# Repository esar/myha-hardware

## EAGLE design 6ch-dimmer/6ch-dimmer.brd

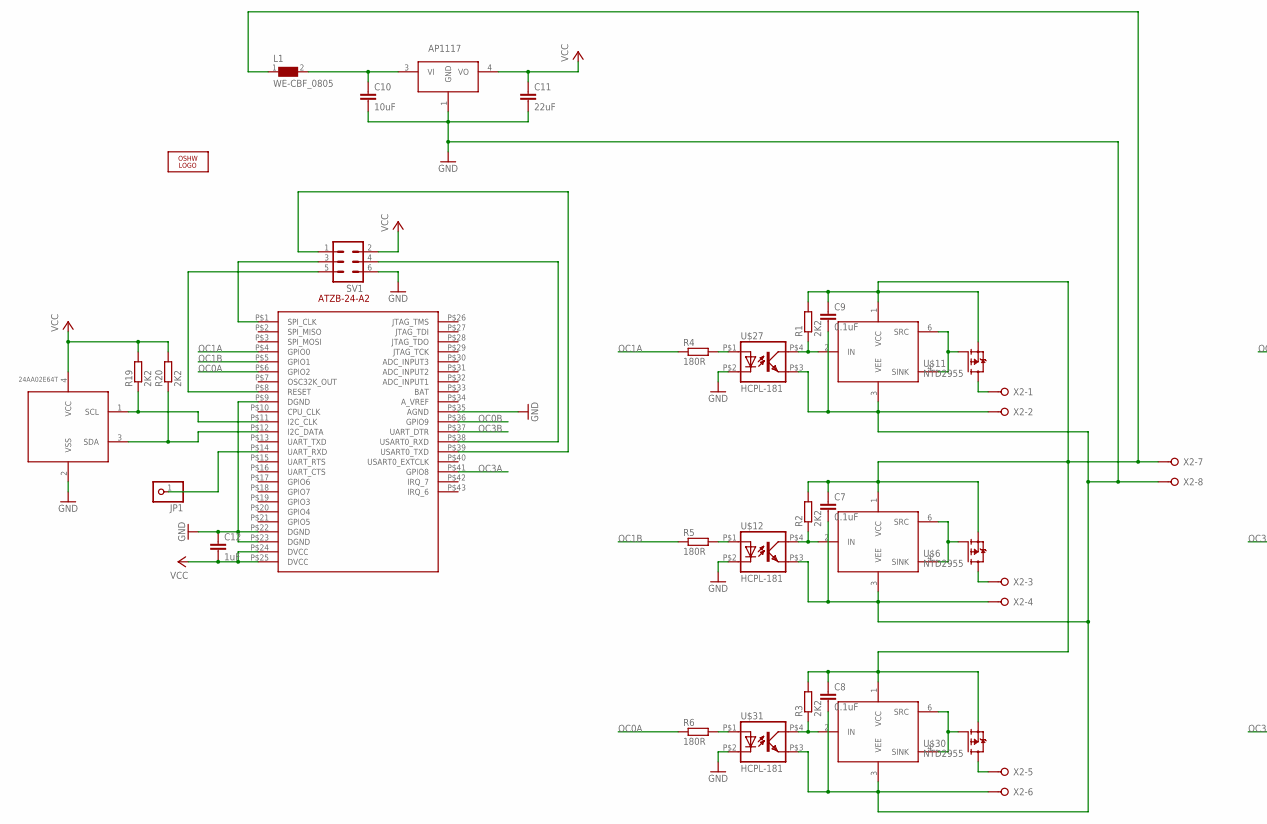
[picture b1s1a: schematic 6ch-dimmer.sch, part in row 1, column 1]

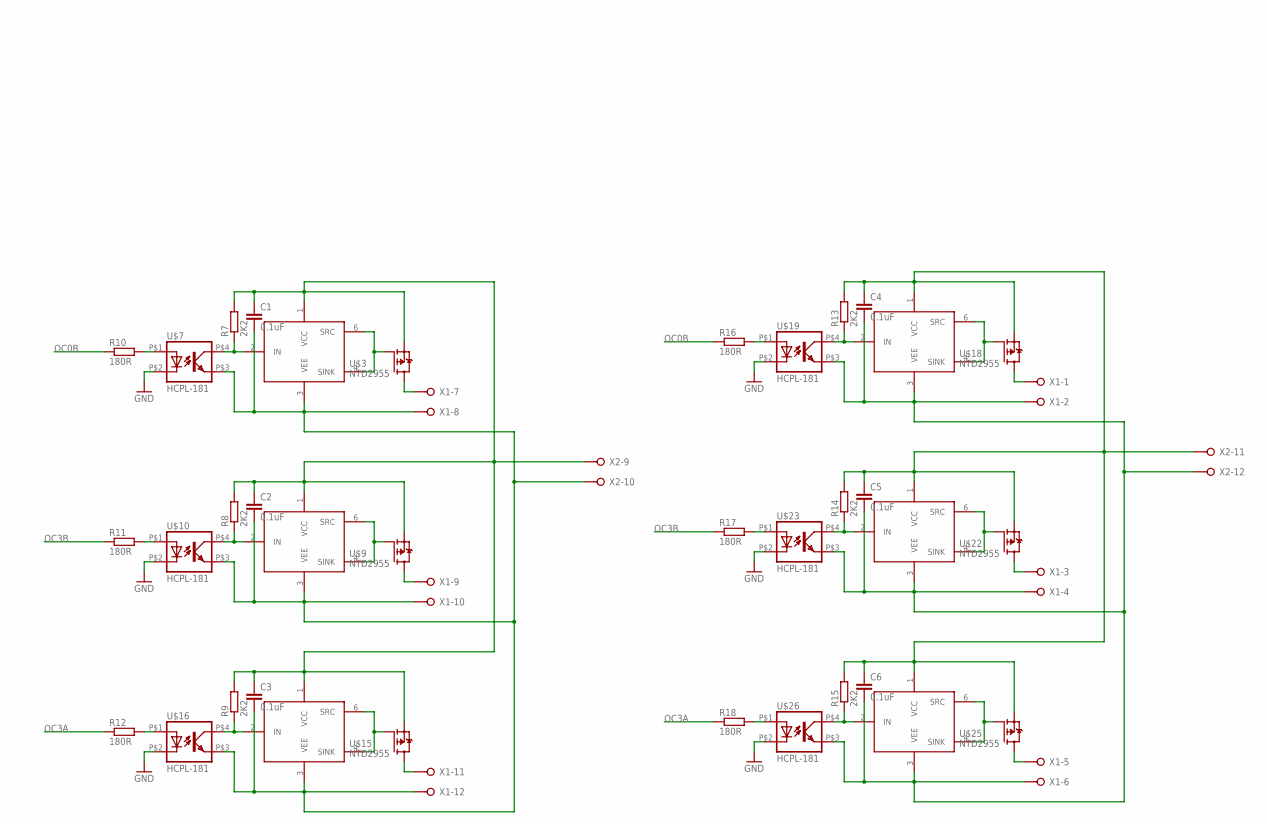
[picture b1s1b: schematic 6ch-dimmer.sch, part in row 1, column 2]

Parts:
C1, C2, C3, C4, C5, C6, C7, C8, C9: 0.1uF; C0603
C10: 10uF; C1210
C11: 22uF; C1210
C12: 1uF; C0603
JP1: PINHD-1X1; 1X01
L1: WE-CBF_0805; 0805
LOGO1: OSHW_LOGO_10MILX0500-NT; OSHW_10X500_NOTEXT
R1, R2, R3, R7, R8, R9, R13, R14, R15, R19, R20: 2K2; R0603
R4, R5, R6, R10, R11, R12, R16, R17, R18: 180R; R0603
SV1: MA03-2
U$1: ATZB-24-A2
U$2, U$4, U$5, U$8, U$13, U$14, U$17, U$21, U$24: ZXGD3005E6; SOT23-6
U$3, U$6, U$9, U$11, U$15, U$18, U$22, U$25, U$30: NTD2955; DPAK
U$7, U$10, U$12, U$16, U$19, U$23, U$26, U$27, U$31: HCPL-181
U$20: 24AA02E64T; SOT23-5L
U$28: AP1117; SOT223
X1, X2: W237-12P

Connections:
GND: C7.2, C8.2, C9.2, C10.2, C11.2, C12.1, SV1.6, U$1.P$9 (DGND), U$1.P$22 (DGND), U$1.P$23 (DGND), U$1.P$35 (AGND), U$4.3 (VEE), U$5.3 (VEE), U$7.P$2 (C), U$10.P$2 (C), U$12.P$2 (C), U$12.P$3 (EMIT), U$13.3 (VEE), U$16.P$2 (C), U$19.P$2 (C), U$20.2 (VSS), U$23.P$2 (C), U$26.P$2 (C), U$27.P$2 (C), U$27.P$3 (EMIT), U$28.1 (GND), U$31.P$2 (C), U$31.P$3 (EMIT), X2.2, X2.4, X2.6, X2.8
unnamed: U$2.4 (SINK), U$2.6 (SRC), U$3.1 (G)
unnamed: R7.1, U$2.2 (IN), U$7.P$4 (COL)
unnamed: U$3.4 (D), X1.7
unnamed: U$4.4 (SINK), U$4.6 (SRC), U$11.1 (G)
unnamed: U$5.4 (SINK), U$5.6 (SRC), U$6.1 (G)
unnamed: R2.1, U$5.2 (IN), U$12.P$4 (COL)
unnamed: U$8.4 (SINK), U$8.6 (SRC), U$9.1 (G)
unnamed: R8.1, U$8.2 (IN), U$10.P$4 (COL)
unnamed: U$9.4 (D), X1.9
unnamed: U$14.4 (SINK), U$14.6 (SRC), U$15.1 (G)
unnamed: R9.1, U$14.2 (IN), U$16.P$4 (COL)
unnamed: C1.1, C2.1, C3.1, R7.2, R8.2, R9.2, U$2.1 (VCC), U$3.3 (S), U$8.1 (VCC), U$9.3 (S), U$14.1 (VCC), U$15.3 (S), X2.9
unnamed: R1.1, U$4.2 (IN), U$27.P$4 (COL)
unnamed: U$11.4 (D), X2.1
unnamed: U$15.4 (D), X1.11
unnamed: R10.2, U$7.P$1 (A)
unnamed: R11.2, U$10.P$1 (A)
unnamed: R12.2, U$16.P$1 (A)
unnamed: JP1.1, U$1.P$14 (UART_RXD)
unnamed: U$6.4 (D), X2.3
unnamed: U$13.4 (SINK), U$13.6 (SRC), U$30.1 (G)
unnamed: R3.1, U$13.2 (IN), U$31.P$4 (COL)
unnamed: C1.2, C2.2, C3.2, U$2.3 (VEE), U$7.P$3 (EMIT), U$8.3 (VEE), U$10.P$3 (EMIT), U$14.3 (VEE), U$16.P$3 (EMIT), X1.8, X1.10, X1.12, X2.10
unnamed: C7.1, C8.1, C9.1, L1.1, R1.2, R2.2, R3.2, U$4.1 (VCC), U$5.1 (VCC), U$6.3 (S), U$11.3 (S), U$13.1 (VCC), U$30.3 (S), X2.7
unnamed: U$17.4 (SINK), U$17.6 (SRC), U$18.1 (G)
unnamed: U$30.4 (D), X2.5
unnamed: R13.1, U$17.2 (IN), U$19.P$4 (COL)
unnamed: U$18.4 (D), X1.1
unnamed: R4.2, U$27.P$1 (A)
unnamed: U$21.4 (SINK), U$21.6 (SRC), U$22.1 (G)
unnamed: R5.2, U$12.P$1 (A)
unnamed: R6.2, U$31.P$1 (A)
unnamed: R14.1, U$21.2 (IN), U$23.P$4 (COL)
unnamed: U$22.4 (D), X1.3
unnamed: U$24.4 (SINK), U$24.6 (SRC), U$25.1 (G)
unnamed: R15.1, U$24.2 (IN), U$26.P$4 (COL)
unnamed: C4.1, C5.1, C6.1, R13.2, R14.2, R15.2, U$17.1 (VCC), U$18.3 (S), U$21.1 (VCC), U$22.3 (S), U$24.1 (VCC), U$25.3 (S), X2.11
unnamed: U$25.4 (D), X1.5
unnamed: R16.2, U$19.P$1 (A)
unnamed: R17.2, U$23.P$1 (A)
unnamed: R18.2, U$26.P$1 (A)
unnamed: C4.2, C5.2, C6.2, U$17.3 (VEE), U$19.P$3 (EMIT), U$21.3 (VEE), U$23.P$3 (EMIT), U$24.3 (VEE), U$26.P$3 (EMIT), X1.2, X1.4, X1.6, X2.12
unnamed: R19.1, U$1.P$11 (I2C_CLK), U$20.1 (SCL)
unnamed: R20.1, U$1.P$12 (I2C_DATA), U$20.3 (SDA)
unnamed: C10.1, L1.2, U$28.3 (VI)
unnamed: SV1.1, U$1.P$39 (USART0_TXD)
unnamed: SV1.4, U$1.P$38 (USART0_RXD)
unnamed: SV1.3, U$1.P$1 (SPI_CLK)
unnamed: SV1.5, U$1.P$8 (RESET)
OC0A: R6.1, U$1.P$6 (GPIO2)
OC0B: R10.1, R16.1, U$1.P$36 (GPIO9)
OC1A: R4.1, U$1.P$4 (GPIO0)
OC1B: R5.1, U$1.P$5 (GPIO1)
OC3A: R12.1, R18.1, U$1.P$41 (GPIO8)
OC3B: R11.1, R17.1, U$1.P$37 (UART_DTR)
VCC: C11.1, C12.2, R19.2, R20.2, SV1.2, U$1.P$24 (DVCC), U$1.P$25 (DVCC), U$20.4 (VCC), U$28.4 (VO)

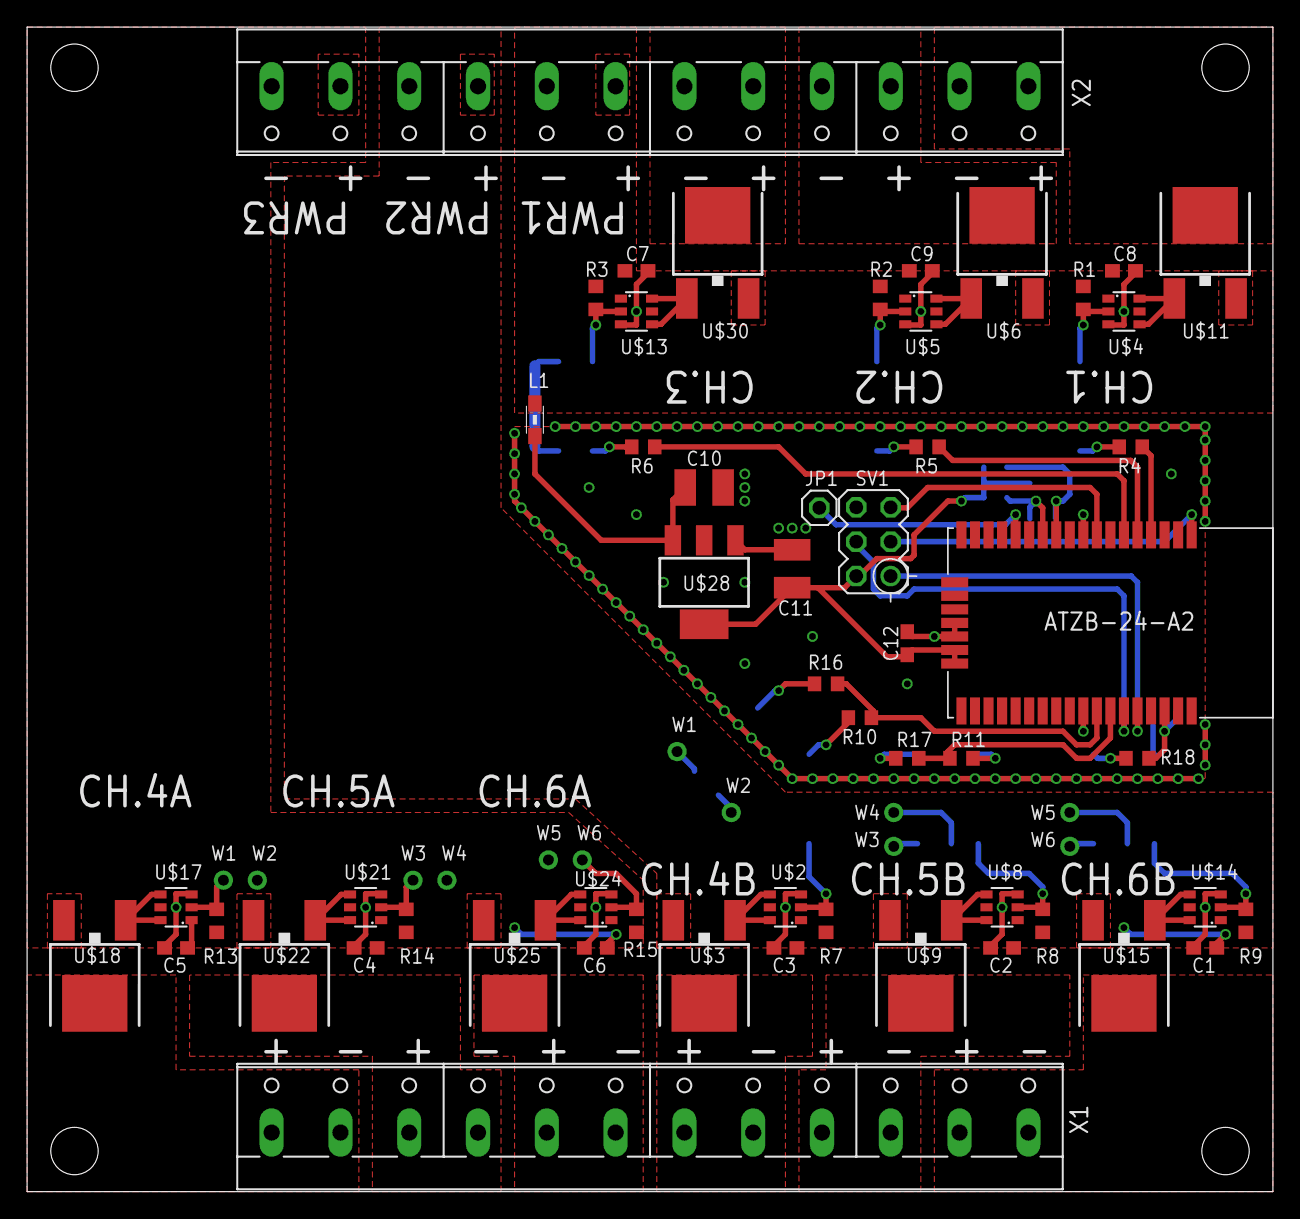
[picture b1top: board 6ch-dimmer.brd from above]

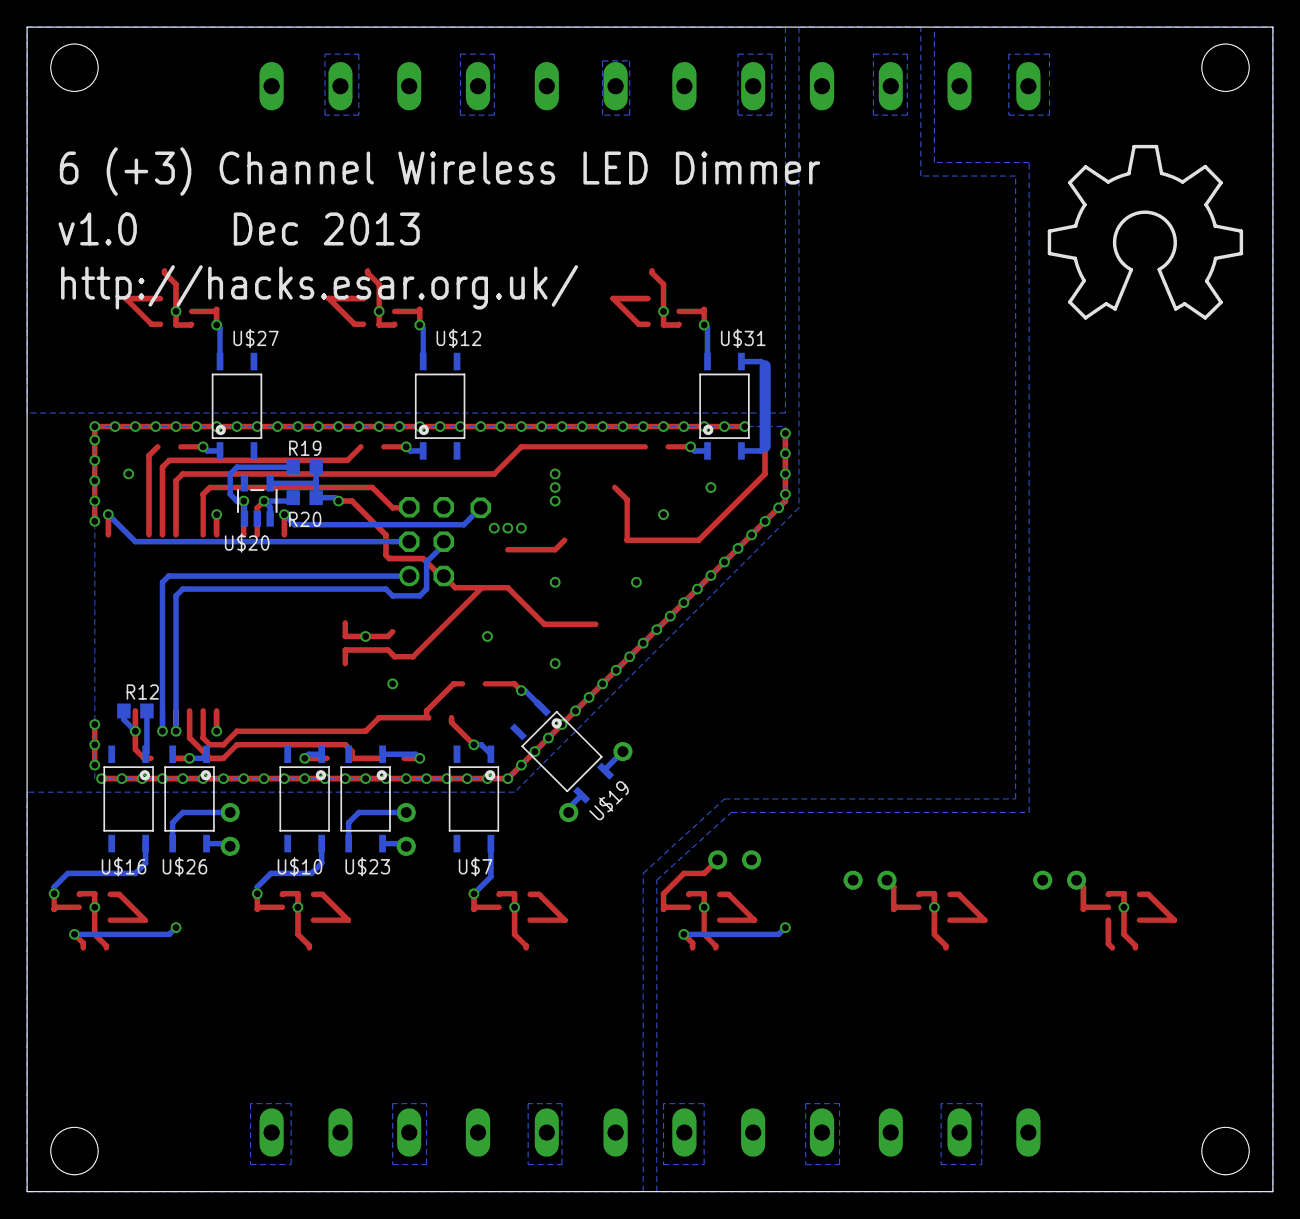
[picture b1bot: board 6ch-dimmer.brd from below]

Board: 2 copper layers, 92.0 x 86.0 mm, 68 parts (14 on the bottom side), 57 nets.

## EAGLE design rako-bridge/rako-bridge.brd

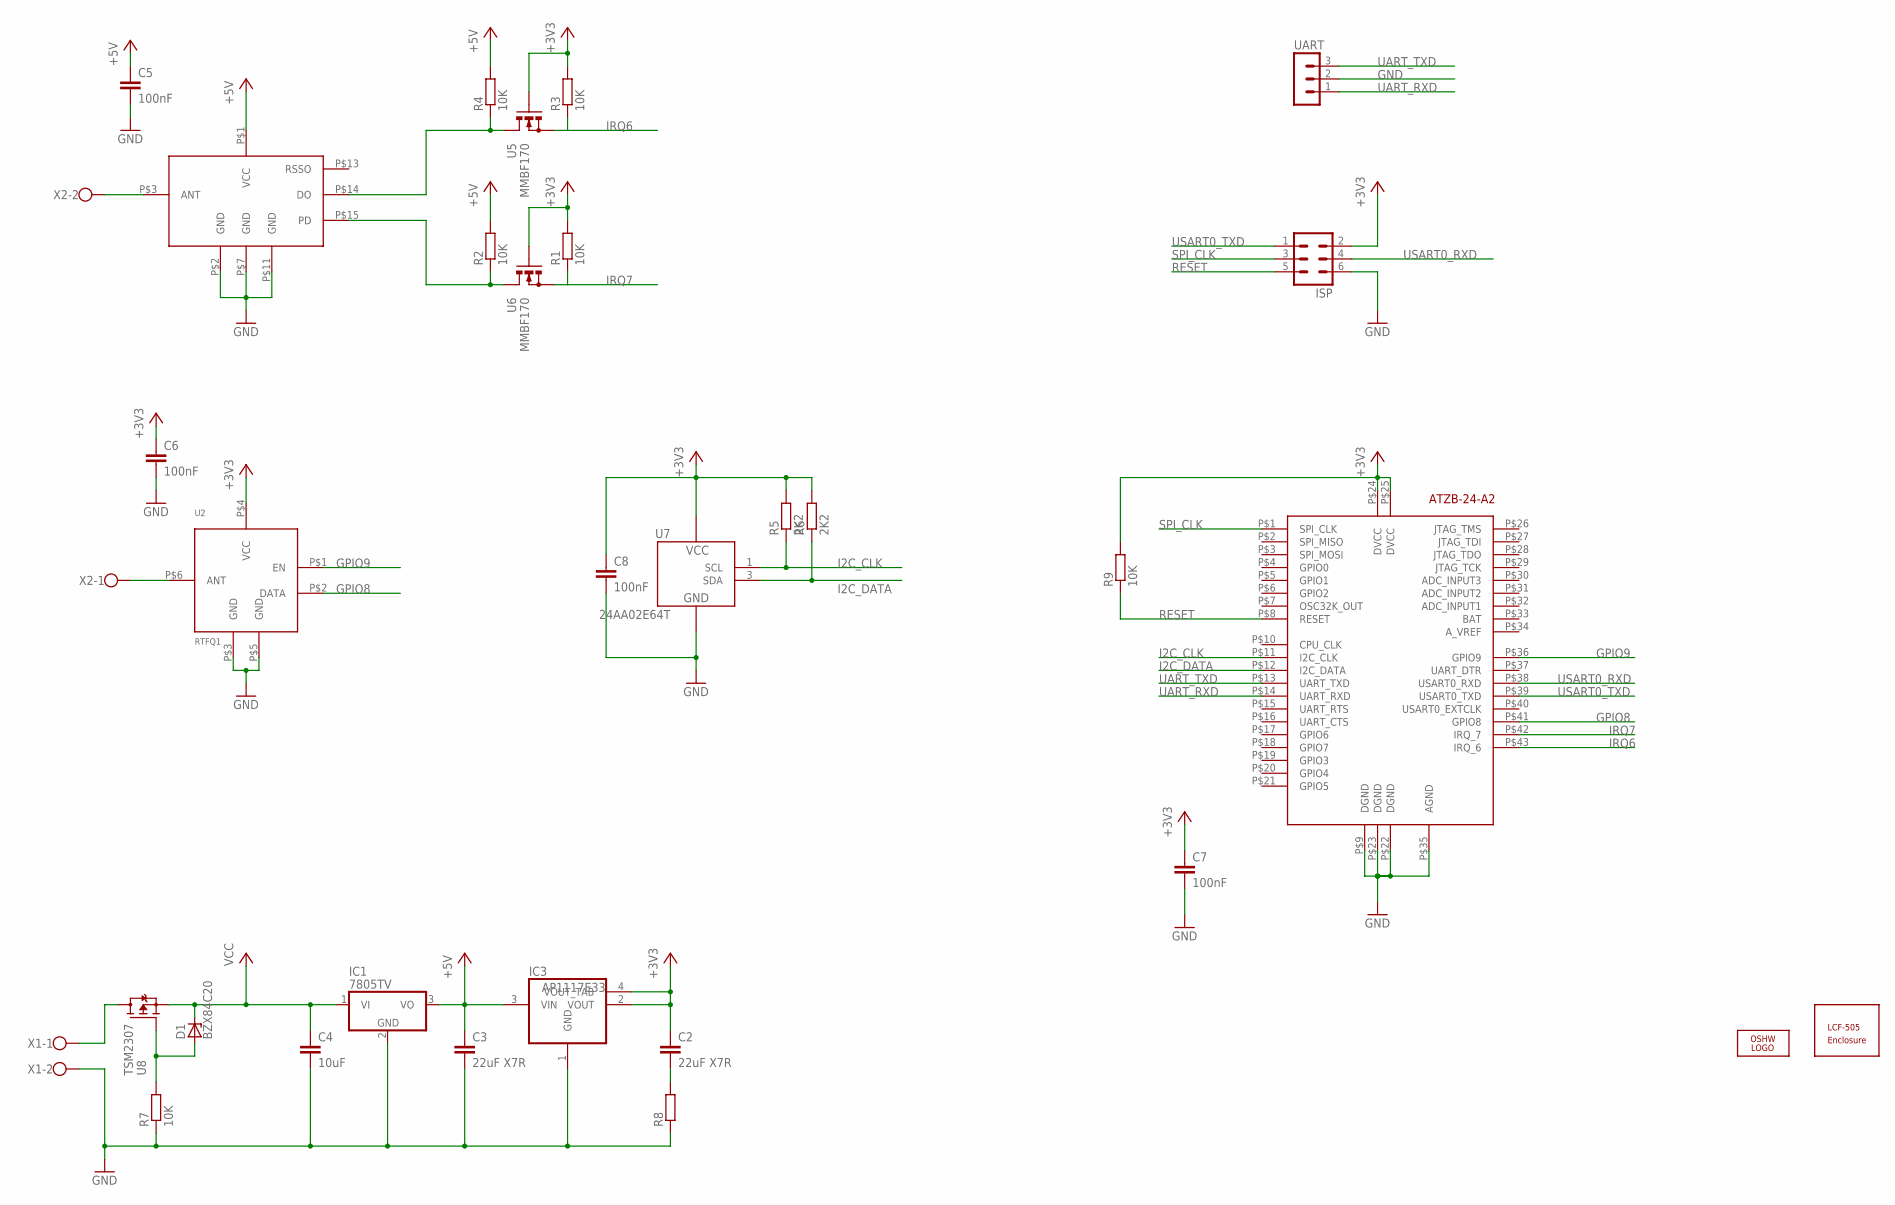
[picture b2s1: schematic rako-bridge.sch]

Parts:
C2, C3: 22uF X7R; C1210
C4: 10uF; C1210
C5, C6, C7, C8: 100nF; C0603
D1: BZX84C20; SOT23
IC1: 7805TV; TO220V
IC3: AP1117E33; SOT223
ISP: MA03-2
LOGO1: OSHW_LOGO_FILLX0200-NT; OSHW_FILLX200_NOTEXT
R1, R2, R3, R4, R7, R9: 10K; R0603
R5, R6: 2K2; R0603
R8: R-EU_R0603; R0603
U2: RTFQ1
U4: RRFQ1
U5, U6: MMBF170; SOT23
U7: 24AA02E64T; SOT23-5L
U8: TSM2307; SOT23
U$1: BOX-LCF-505
U$3: ATZB-24-A2
UART: MA03-1
X1, X2: W237-102

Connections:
+3V3: C2.1, C6.1, C7.1, C8.1, IC3.2 (VOUT), IC3.4 (VOUT_TAB), ISP.2, R1.2, R3.2, R5.2, R6.2, R9.2, U2.P$4 (VCC), U5.1 (G), U6.1 (G), U7.4 (VCC), U$3.P$24 (DVCC), U$3.P$25 (DVCC)
+5V: C3.1, C5.1, IC1.3 (VO), IC3.3 (VIN), R2.2, R4.2, U4.P$1 (VCC)
GND: C3.2, C4.2, C5.2, C6.2, C7.2, C8.2, IC1.2 (GND), IC3.1 (GND), ISP.6, R7.1, R8.1, U2.P$3 (GND), U2.P$5 (GND), U4.P$2 (GND), U4.P$7 (GND), U4.P$11 (GND), U7.2 (VSS), U$3.P$9 (DGND), U$3.P$22 (DGND), U$3.P$23 (DGND), U$3.P$35 (AGND), UART.2, X1.2
GPIO8: U2.P$2 (DATA), U$3.P$41 (GPIO8)
GPIO9: U2.P$1 (EN), U$3.P$36 (GPIO9)
I2C_CLK: R5.1, U7.1 (SCL), U$3.P$11 (I2C_CLK)
I2C_DATA: R6.1, U7.3 (SDA), U$3.P$12 (I2C_DATA)
IRQ6: R3.1, U5.2 (S), U$3.P$43 (IRQ_6)
IRQ7: R1.1, U6.2 (S), U$3.P$42 (IRQ_7)
unnamed: U4.P$3 (ANT), X2.2
unnamed: U2.P$6 (ANT), X2.1
unnamed: D1.1 (A), R7.2, U8.1 (G)
unnamed: U8.3 (D), X1.1
unnamed: R2.1, U4.P$15 (PD), U6.3 (D)
unnamed: R4.1, U4.P$14 (DO), U5.3 (D)
unnamed: C2.2, R8.2
RESET: ISP.5, R9.1, U$3.P$8 (RESET)
SPI_CLK: ISP.3, U$3.P$1 (SPI_CLK)
UART_RXD: U$3.P$14 (UART_RXD), UART.1
UART_TXD: U$3.P$13 (UART_TXD), UART.3
USART0_RXD: ISP.4, U$3.P$38 (USART0_RXD)
USART0_TXD: ISP.1, U$3.P$39 (USART0_TXD)
VCC: C4.1, D1.3 (C), IC1.1 (VI), U8.2 (S)

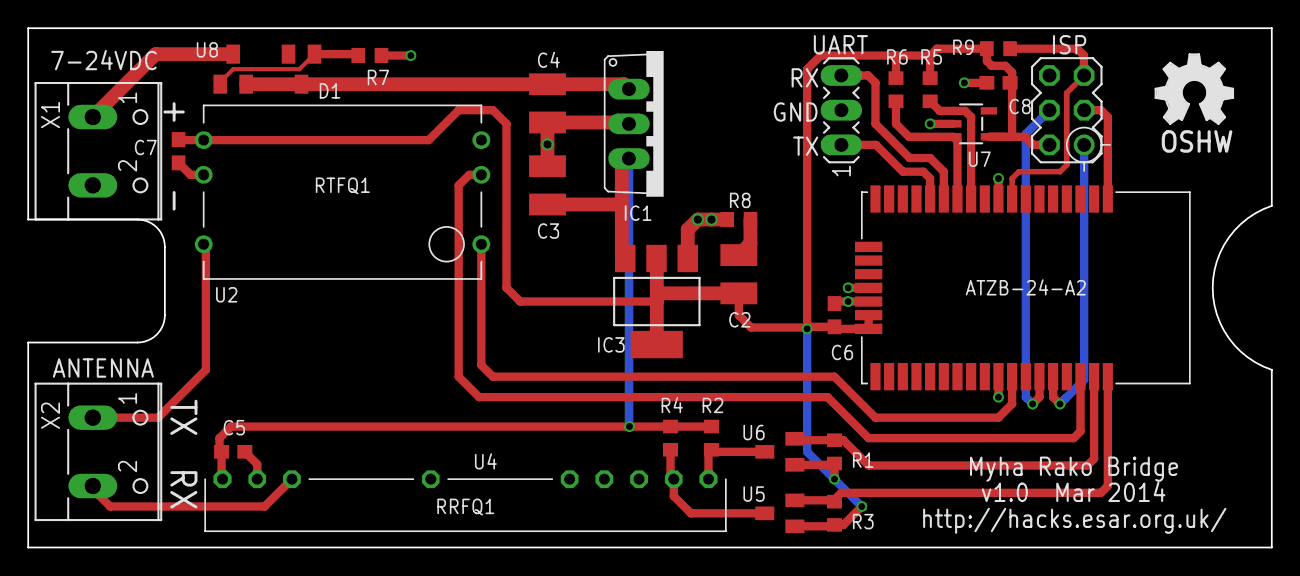
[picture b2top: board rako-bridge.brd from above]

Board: 2 copper layers, 91.0 x 38.0 mm, 32 parts (0 on the bottom side), 23 nets.

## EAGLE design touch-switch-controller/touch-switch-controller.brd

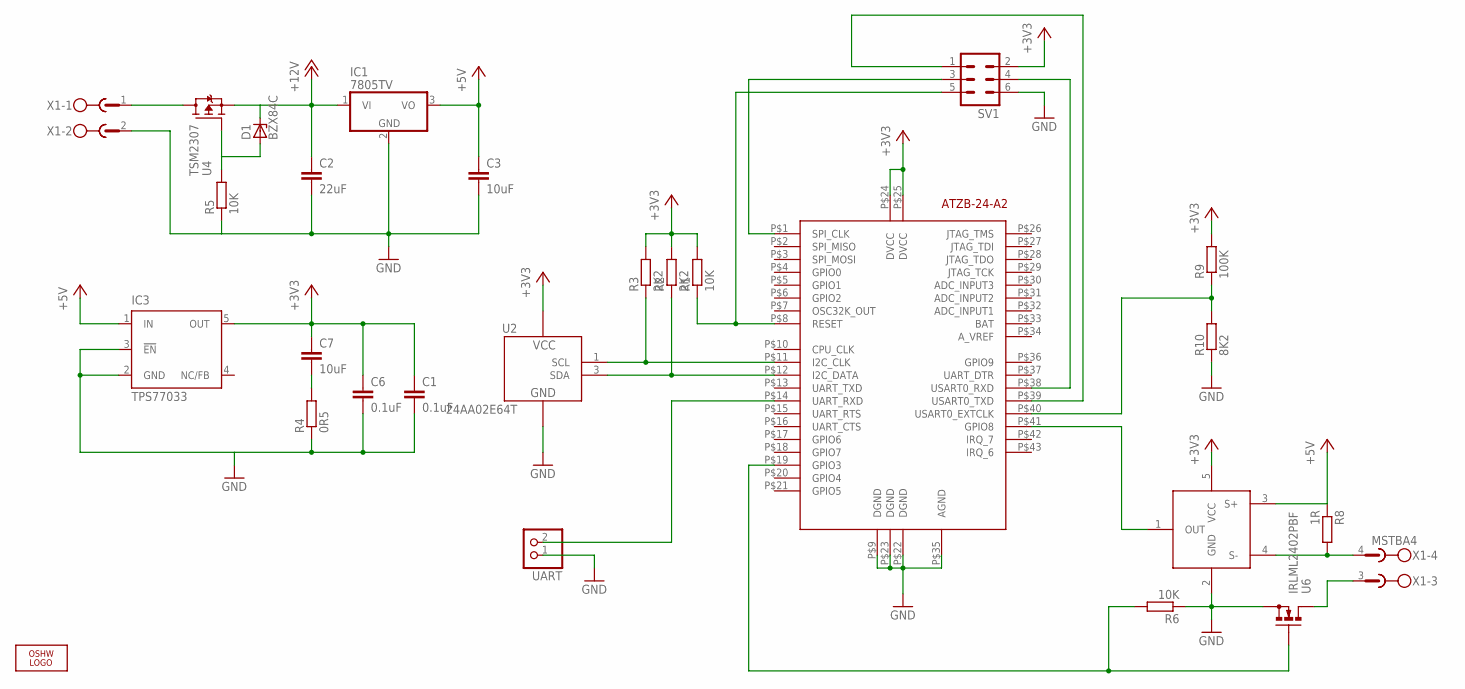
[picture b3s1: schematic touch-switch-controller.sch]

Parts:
C1, C6: 0.1uF; C0603
C2: 22uF; C1210
C3, C7: 10uF; C1210
D1: BZX84C; SOT23
IC1: 7805TV; TO220V
IC3: TPS77033; SOT23-DBV
LOGO1: OSHW_LOGO_FILLX0100-NT; OSHW_FILLX100_NOTEXT
R1, R5, R6: 10K; R0603
R2, R3: 2K2; R0603
R4: 0R5; R0603
R8: 1R; R0603
R9: 100K; R0603
R10: 8K2; R0603
SV1: MA03-2
U1: ZXCT1086; SOT23-5L
U2: 24AA02E64T; SOT23-5L
U4: TSM2307; SOT23
U6: IRLML2402PBF; SOT23
U$3: ATZB-24-A2
UART: PINHD-1X2; 1X02
X1: MSTBA4

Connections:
+3V3: C1.1, C6.1, C7.1, IC3.5 (OUT), R1.2, R2.2, R3.2, R9.2, SV1.2, U1.5 (VCC), U2.4 (VCC), U$3.P$24 (DVCC), U$3.P$25 (DVCC)
+5V: C3.1, IC1.3 (VO), IC3.1 (IN), R8.1, U1.3 (S+)
+12V: C2.1, D1.3 (C), IC1.1 (VI), U4.2 (S)
GND: C1.2, C2.2, C3.2, C6.2, IC1.2 (GND), IC3.2 (GND), IC3.3 (!EN), R4.1, R5.1, R6.1, R10.1, SV1.6, U1.2 (GND), U2.2 (VSS), U6.2 (S), U$3.P$9 (DGND), U$3.P$22 (DGND), U$3.P$23 (DGND), U$3.P$35 (AGND), UART.1, X1.2
unnamed: R9.1, R10.2, U$3.P$40 (USART0_EXTCLK)
unnamed: U1.1 (OUT), U$3.P$41 (GPIO8)
unnamed: R6.2, U6.1 (G), U$3.P$19 (GPIO3)
unnamed: U4.3 (D), X1.1
unnamed: SV1.1, U$3.P$39 (USART0_TXD)
unnamed: SV1.4, U$3.P$38 (USART0_RXD)
unnamed: R3.1, U2.1 (SCL), U$3.P$11 (I2C_CLK)
unnamed: SV1.3, U$3.P$1 (SPI_CLK)
unnamed: R1.1, SV1.5, U$3.P$8 (RESET)
unnamed: R2.1, U2.3 (SDA), U$3.P$12 (I2C_DATA)
unnamed: C7.2, R4.2
unnamed: D1.1 (A), R5.2, U4.1 (G)
unnamed: U$3.P$14 (UART_RXD), UART.2
unnamed: U6.3 (D), X1.3
unnamed: R8.2, U1.4 (S-), X1.4

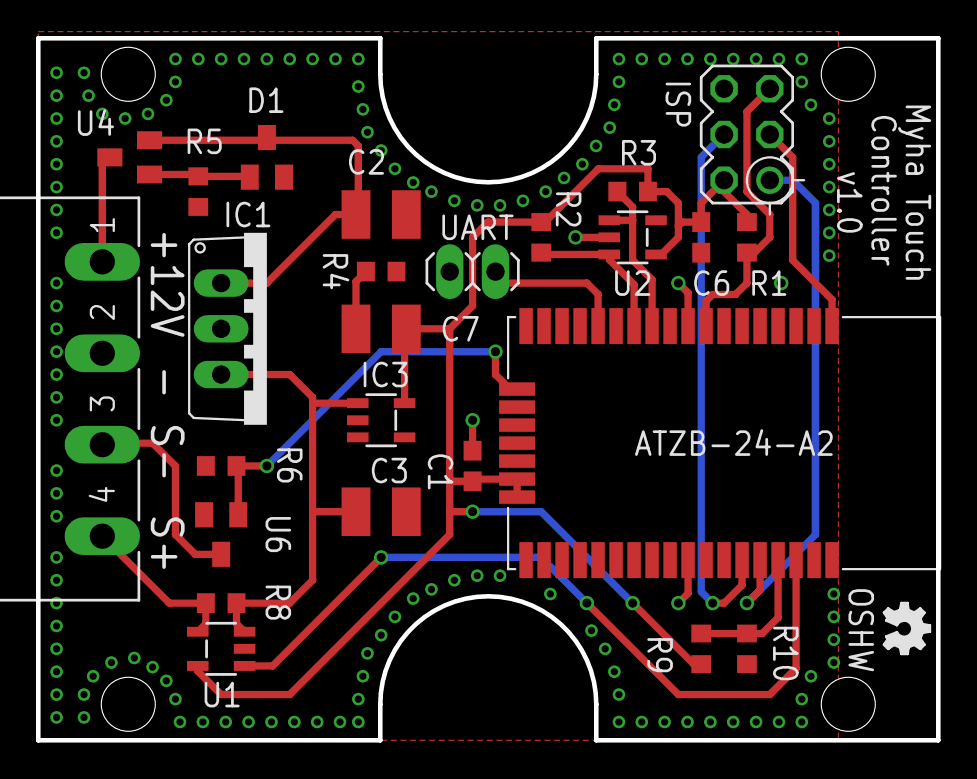
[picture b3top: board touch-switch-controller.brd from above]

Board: 2 copper layers, 50.0 x 39.0 mm, 26 parts (0 on the bottom side), 19 nets.

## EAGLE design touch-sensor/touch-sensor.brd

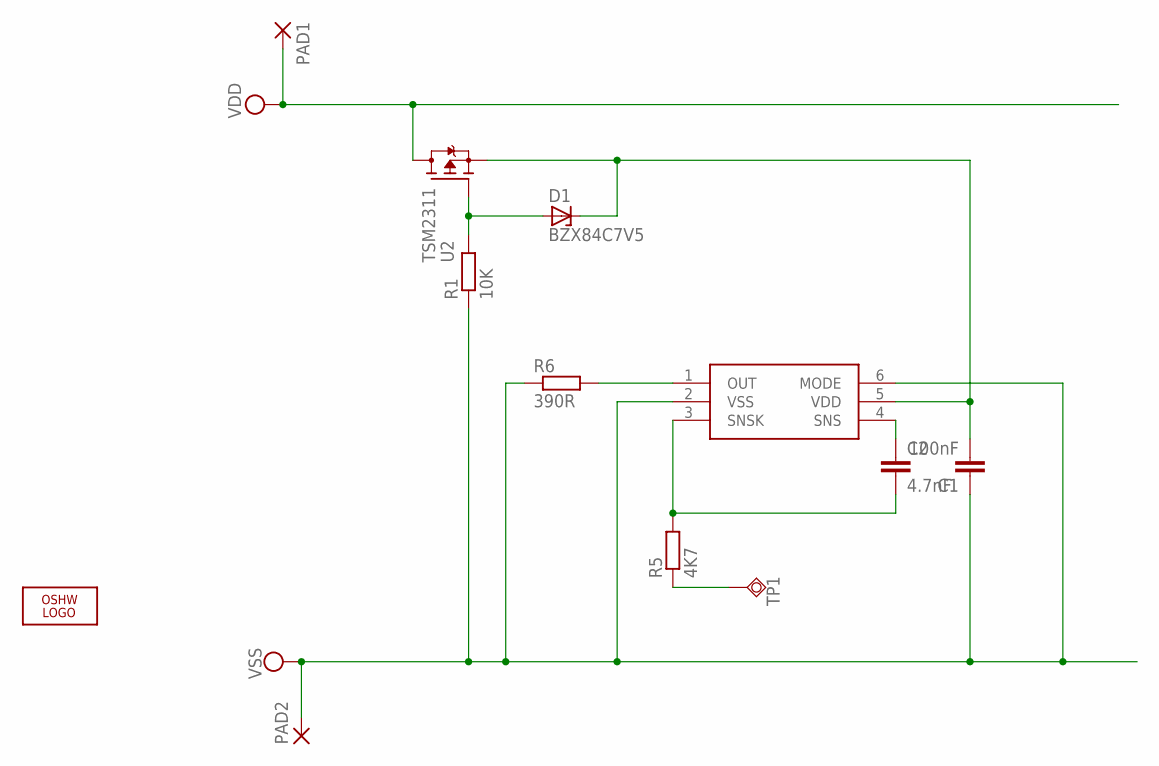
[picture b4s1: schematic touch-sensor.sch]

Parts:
C1: 100nF; C0603
C2: 4.7nF; C0603
D1: BZX84C7V5; SOT23
LOGO1: OSHW_LOGO_10MILX0200-NT; OSHW_10X200_NOTEXT
PAD1, PAD2: 3,81/1,3
R1: 10K; R0603
R5: 4K7; R0603
R6: 390R; R0603
TP1: TPSQTP20SQ; TP20SQ
U1: AT42QT1011; SOT23-6
U2: TSM2311; SOT23

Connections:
unnamed: C1.2, D1.3 (C), U1.5 (VDD), U2.2 (S)
unnamed: D1.1 (A), R1.2, U2.1 (G)
unnamed: C2.1, U1.4 (SNS)
unnamed: C2.2, R5.2, U1.3 (SNSK)
unnamed: R6.2, U1.1 (OUT)
unnamed: R5.1, TP1.TP
VDD: PAD1.1, U2.3 (D)
VSS: C1.1, PAD2.1, R1.1, R6.1, U1.2 (VSS), U1.6 (MODE)

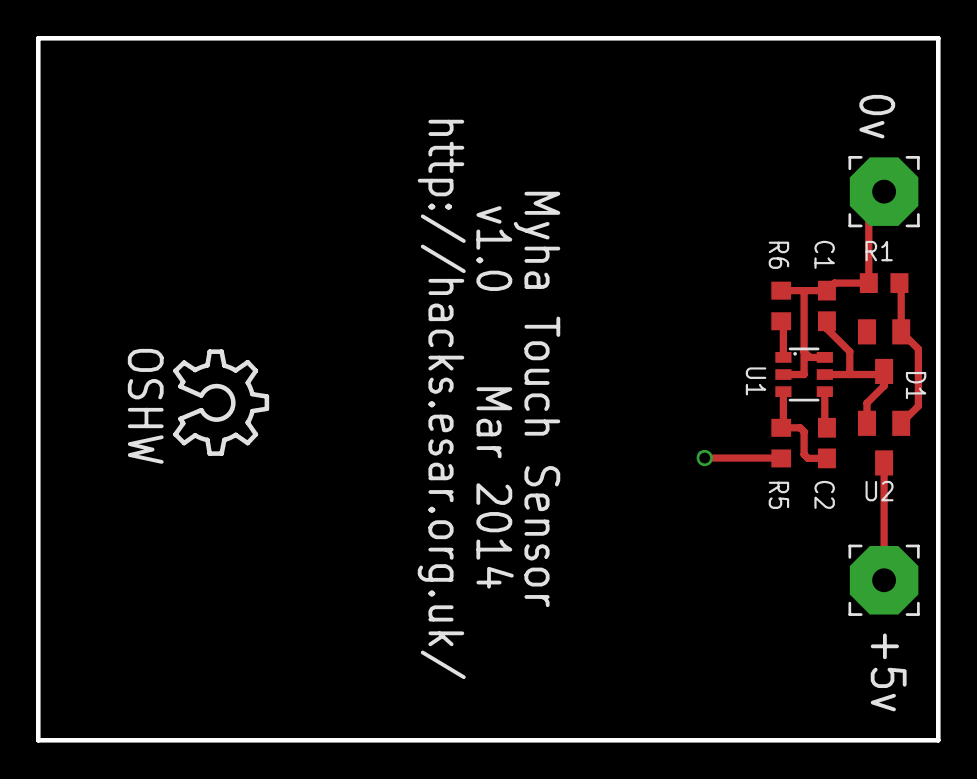
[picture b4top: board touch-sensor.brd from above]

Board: 2 copper layers, 50.0 x 39.0 mm, 12 parts (1 on the bottom side), 8 nets.

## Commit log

2014-06-04 touch-sensor: added initial files
2014-06-04 touch-switch-controller: added initial files
2014-06-04 rako-bridge: added initial files
2014-06-04 pi-radio: added initial files
2014-06-04 6ch-dimmer: added initial files

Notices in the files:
parts and their libraries:
EagleLibrary_Wuerth_Elektronik_eiSos_Ver: Copyright: Würth Elektronik
